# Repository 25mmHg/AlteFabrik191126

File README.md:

# AlteFabrik191126
 Flimmerfeen2.0 likes to be in groups

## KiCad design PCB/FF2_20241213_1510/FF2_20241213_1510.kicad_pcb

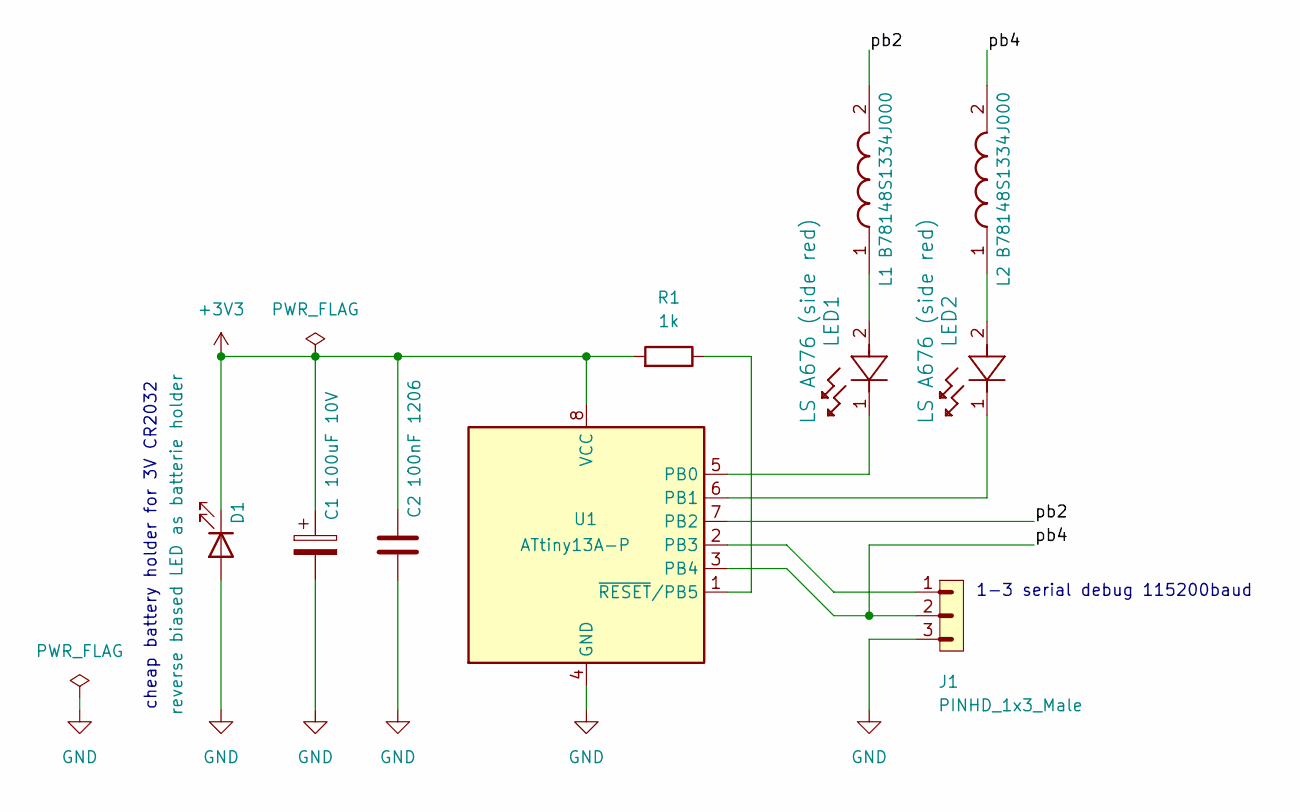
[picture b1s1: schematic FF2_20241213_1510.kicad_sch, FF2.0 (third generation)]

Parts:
C1: 100uF 10V; CP_Radial_D5.0mm_P2.50mm
C2: 100nF 1206; C_0805_2012Metric_Pad1.15x1.40mm_HandSolder
D1: reverse biased LED as batterie holder; LED_D5.0mm_Clear
J1: PINHD_1x3_Male; PinHeader_1x03_P2.54mm_Vertical
L1, L2: B78148S1334J000; B78148S; Mouser Part Number 871-B78148S1334J000
LED1, LED2: LS A676 (side red); LED_LS A676-P2S1-1-0-20-R33-Z_AOS
R1: 1k; R_0805_2012Metric_Pad1.15x1.40mm_HandSolder
U1: ATtiny13A-P; DIP-8_W7.62mm

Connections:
+3V3: C1.1, C2.1, D1.1 (K), R1.1, U1.8 (VCC)
/pb2: L1.2, U1.7 (PB2)
/pb4: J1.2, L2.2, U1.3 (PB4)
GND: C1.2, C2.2, D1.2 (A), J1.3, U1.4 (GND)
unnamed: L1.1, LED1.2
unnamed: L2.1, LED2.2
unnamed: LED1.1, U1.5 (PB0)
unnamed: LED2.1, U1.6 (PB1)
unnamed: J1.1, U1.2 (PB3)
unnamed: R1.2, U1.1 (~RESET/PB5)

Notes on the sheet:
cheap battery holder for 3V CR2032
1-3 serial debug 115200baud

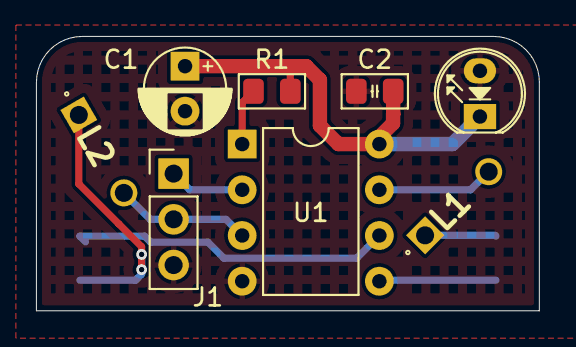
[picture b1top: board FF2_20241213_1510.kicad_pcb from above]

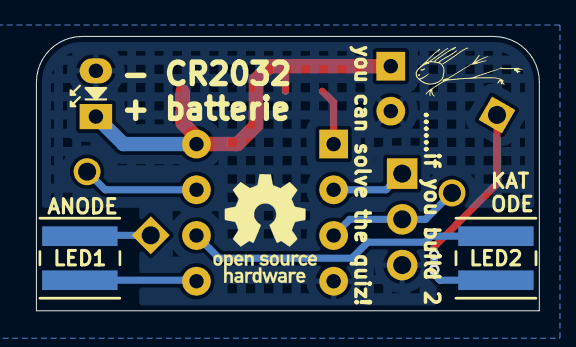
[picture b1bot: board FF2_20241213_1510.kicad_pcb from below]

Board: 2 copper layers, 27.9 x 15.2 mm, 10 parts (2 on the bottom side), 10 nets.

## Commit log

2020-08-17 Create LICENSE
2020-09-05 change 2files
2022-02-12 change files
2024-12-14 add pcb-files
    i design a small PCB 4 the puzzle
2024-12-14 add link
